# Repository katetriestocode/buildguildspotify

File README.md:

This is the spotify (ew f daniel ek) display i made for buildguild... and then worked on more :P
instead of spotify, it is a pomodoro style study buddy tamagotchi!
It features a tft 1.8" 160x128 screen, a lolin mini esp32, and 3 buttons.
The tamagotchi works so that it encourages study sessions of 30 mins with 5 mins break, switching between different faces such as idle, locked in and tired (which he becomes after studying more than half an hour without breaks, and regenerates energy after a 5 min break) :)
It also displays current study time, current break time left, and total study time.

And this is the background:

And this is the case:

with switches and without lid:

completely taken apart:

alsooo here is the wiring diagram:

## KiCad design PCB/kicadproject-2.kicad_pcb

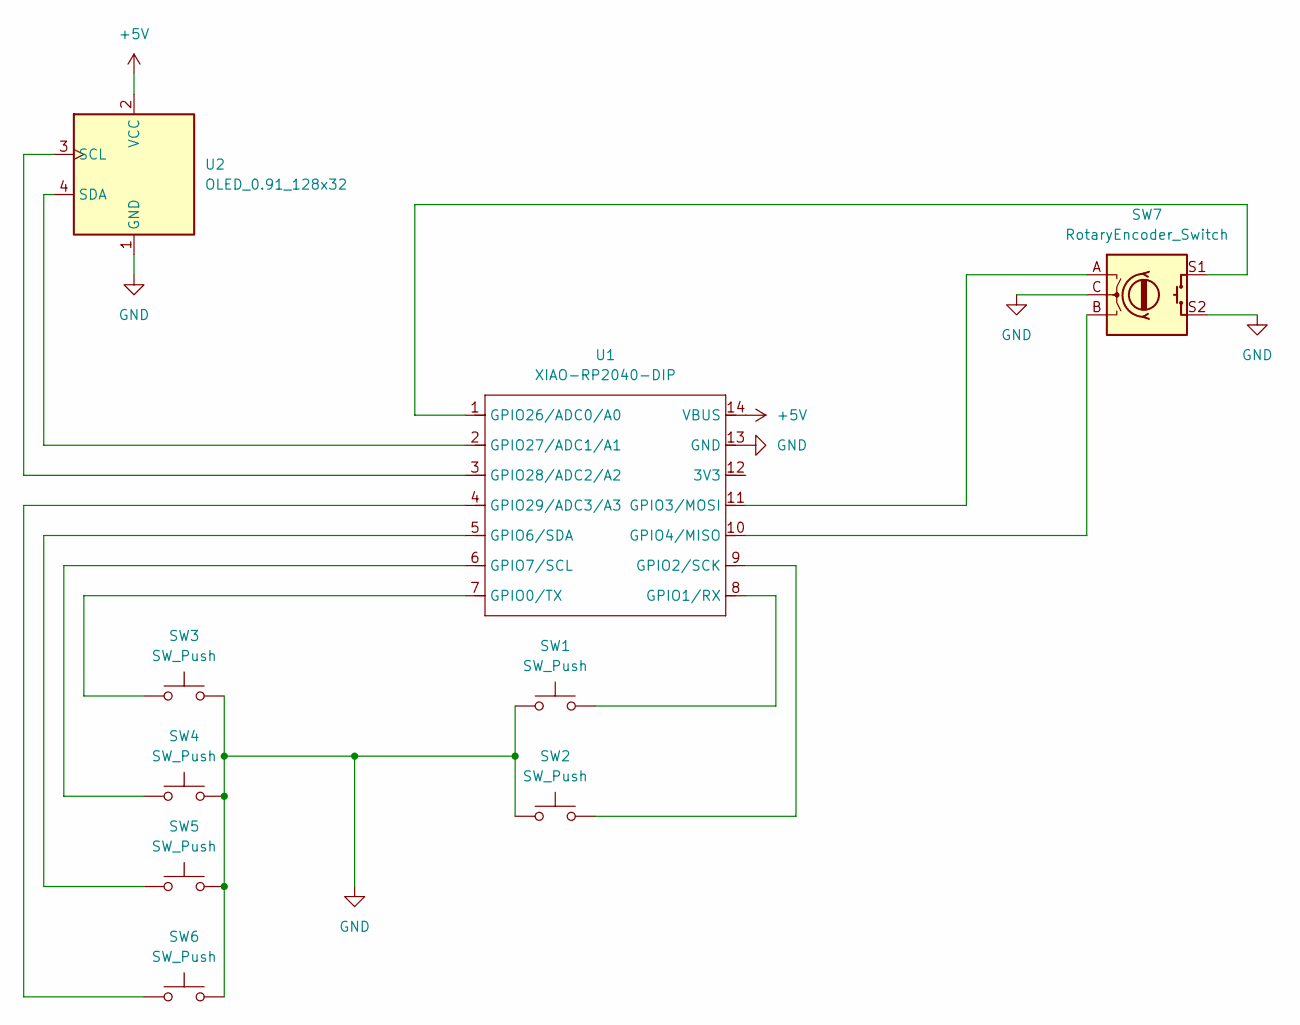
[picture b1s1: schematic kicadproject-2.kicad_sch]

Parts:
SW1, SW2, SW3, SW4, SW5, SW6: SW_Push; SW_Cherry_MX_1.00u_PCB
SW7: RotaryEncoder_Switch; RotaryEncoder_Alps_EC11E-Switch_Vertical_H20mm
U1: XIAO-RP2040-DIP
U2: OLED_0.91_128x32

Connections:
+5V: U1.14 (VBUS), U2.2 (VCC)
GND: SW1.1, SW2.1, SW3.2, SW4.2, SW5.2, SW6.2, SW7.C, SW7.S2, U1.13 (GND), U2.1 (GND)
unnamed: SW3.1, U1.7 (GPIO0/TX)
unnamed: SW1.2, U1.8 (GPIO1/RX)
unnamed: SW2.2, U1.9 (GPIO2/SCK)
unnamed: SW7.A, U1.11 (GPIO3/MOSI)
unnamed: SW7.B, U1.10 (GPIO4/MISO)
unnamed: SW5.1, U1.5 (GPIO6/SDA)
unnamed: SW4.1, U1.6 (GPIO7/SCL)
unnamed: SW7.S1, U1.1 (GPIO26/ADC0/A0)
unnamed: U1.2 (GPIO27/ADC1/A1), U2.4 (SDA)
unnamed: U1.3 (GPIO28/ADC2/A2), U2.3 (SCL)
unnamed: SW6.1, U1.4 (GPIO29/ADC3/A3)

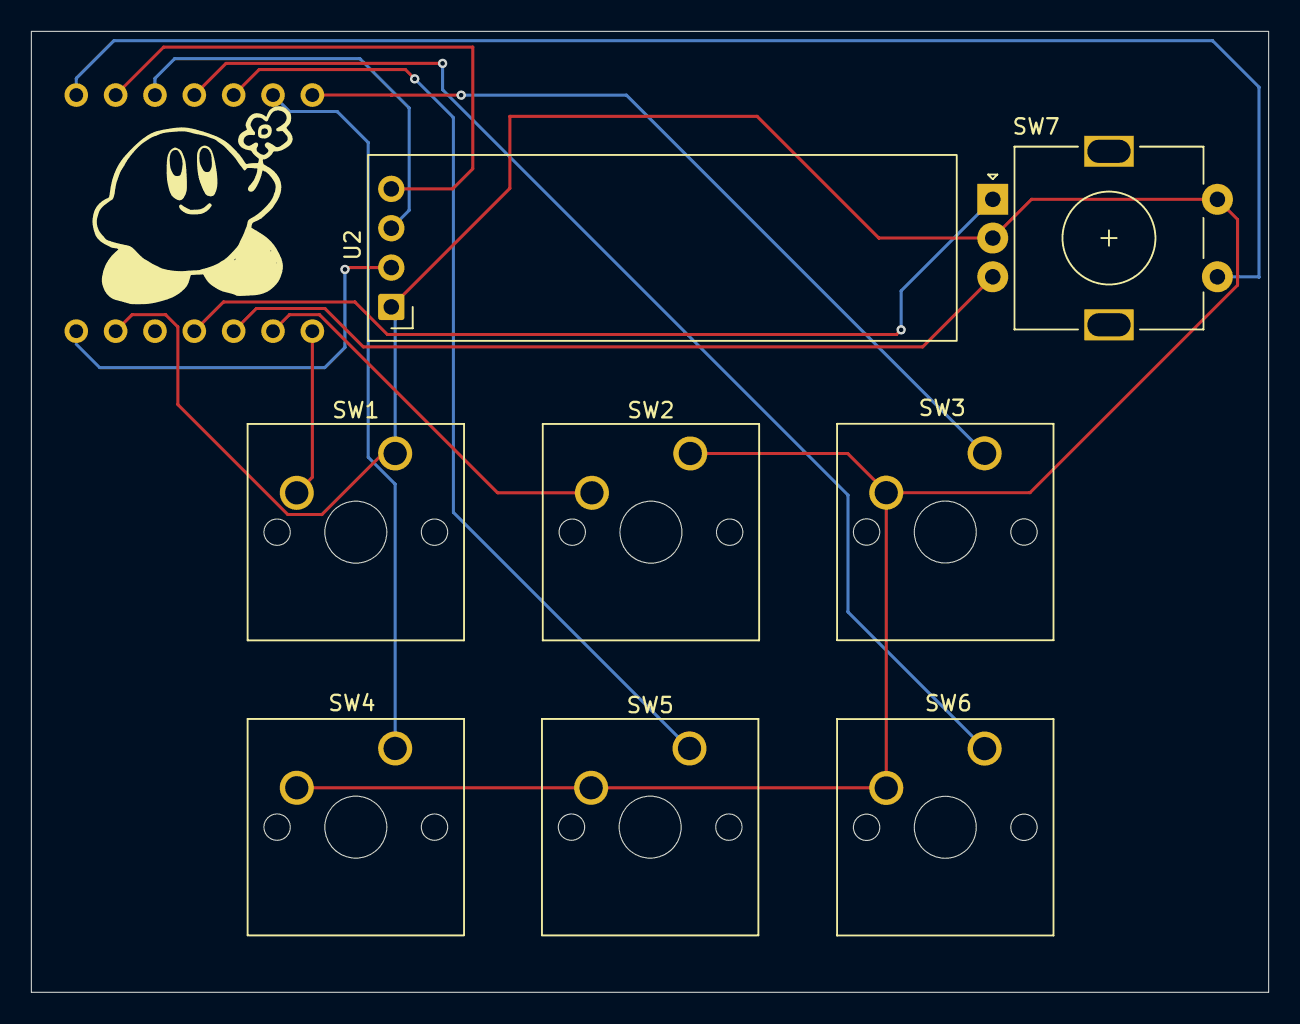
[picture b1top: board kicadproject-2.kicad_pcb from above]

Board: 2 copper layers, 79.9 x 62.0 mm, 10 parts (1 on the bottom side), 13 nets.

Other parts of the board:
logo: LOGO; kirbysmaller

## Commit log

2026-04-16 font update
2026-04-23 purge
2026-05-02 logic added
2026-05-02 badoop
2026-05-02 bedoop
2026-05-02 wth??????
2026-05-02 f it we ball ig
2026-05-02 readme'ed!
2026-05-02 badabim dababum
2026-05-02 badeepdapdoop
2026-05-02 plsplspls
2026-05-02 BOOP
